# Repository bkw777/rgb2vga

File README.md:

# rgb2vga
Convert 15khz RGB to 31khz VGA

Uses Altera DE0-Nano FPGA development board to convert analog 15Khz RGB signal to VGA 31Khz 256 color.

This is a modified version of the original [RGB2VGA by Luis Felipe da Costa Antoniosi](https://sites.google.com/site/tandycocoloco/fpga-rgb2vga).  
<!-- (Archived original site [archive.org](https://web.archive.org/web/https://sites.google.com/site/tandycocoloco/rgb2vga)) -->

The electronics and fpga code are the same as the original.

The resistor values are from [Roger Taylor](http://www.cococommunity.net/vga-for-the-coco-3/).

The physical layout is changed to make a more compact package and to build-in the two modifications described in the original docs.

The schematic and pcb layout are re-drawn from scratch in KiCad to provide editable source files.

The VHDL source is just a fork of [the original](https://github.com/lfantoniosi/rgb2vga) but with all of the non-source files cleaned out.  
The VHDL does compile and you can generate a new working rgb2vga.jic from it. But as noted by Roger Taylor, you may want to use the original JIC file from Luis anyway because it may be more stable. There is a preseved copy of Luis's original rgb2vga.jic in [vhdl/Original_JIC](vhdl/Original_JIC).

The enclosure is mine, and the OpenSCAD source is included.

Video showing v003 in action.  

Alternate enclosure top with screws and nuts for the artifact switch instead of melted posts.

<!-- [PCB from OSHPark]()  -->
[PCB and Enclosure from PCBWAY](https://www.pcbway.com/project/shareproject/de0_nano_fpga_rgb2vga.html)  

[BOM from DigiKey](https://www.digikey.com/short/wv89d9fv)  

The BOM does not include R29 or C4, which you normally do not populate.  
<!-- 
R29 and C4 provide a 500khz lowpass filter from the LM1881 datasheet.  
If you want to add the lowpass filter, remember to cut the trace in the middle of the R29 footprint.  
I have no idea if the lowpass filter is desired or not. It's in the LM1881 datasheet and it sounds like a good idea since the computer is full of 1+ mhz signals, but I have not actually tested that addition yet.
-->

<!-- 
[DE0-Nano](http://www.terasic.com.tw/cgi-bin/page/archive.pl?Language=English&No=593)
When searching other sources like ebay, don't accidentally get **DE0-Nano-SoC**, that's something else.
-->

<!--
## Through-Hole Version

[Through-Hole BOM from DigiKey](https://www.digikey.com/short/5mq32b7z)
-->

[PCB Gerbers, FPGA Firmware, Enclosure STLs](../../releases/)

# Directions  
## Building the PCB  
- Remove pin #6 from the 2x5 coco3 rgb connector before soldering. Pin #6 is the center pin on the bottom row, opposite/away from the polarity notch.  
- Solder trim pot R24 on the bottom side, and flush cut and re-flow to smooth domes, before R13, R15, R16.  
- Solder the LM1881 U1 before any of the other parts around it.  
- Solder the Artifact switch SW2 before the 3-pin header J7.  
- Solder remaining parts in any order.  

## Programming the DE0-Nano  
Below is the minimum directions and minimum download possible, using the stand-alone Quartus programmer app and the pre-compiled firmware.  
Alternatively, [compile the firmware from the vhdl source](compile_vhdl.md).

### Install the Quartus Standalone Programmer  
https://fpgasoftware.intel.com/  
Select edition: Lite -> Additional Software -> Quartus Prime Programmer and Tools  
(For Linux, install: Individual Files -> Quartus Prime, not the stand-alone programmer package. The stand-alone Quartus programmer package for Linux is broken, missing ```libprotobuf.so.14.0.0```)

### Download the firmware
Download ```rgb2vga.jic``` from [releases](../../releases/)  

### Program the DE0-Nano  
Connect the usb cable  
Launch the Quartus Programmer app  
Hardware Setup... -> USB-Blaster  
Add File... -> ```rgb2vga.jic```  
Tick "Program/Configure"  
Start  

## Assemble
- Remove the acrylic cover and short upper stand-offs from the DE0-Nano. If using the printed enclosure, remove the lower stand-offs too. If not using the printed enclosure, keep the longer bottom standoffs, replace the short upper standoffs with the screws from the cover.  
- Put the RGB2VGA and DE0-Nano together with the trim pot on the same side as the USB connector.  
- For TANDY Color Computer 3, turn all dip switches off. For most games, turn the Artifact switch on. If using the printed enclosure with enclosure artifact switch, set the pcb artifact switch to OFF.  
- Turn the trim pot to 50%.  
- Insert the IDC pin block-off plugs into pin #6 on each end of the ribbon cable. Pin #6 is the center pin on the row opposite/away from the the polarity bump.  

## Enclosure
The source for the enclosure is the [rgb2vga.scad](case/rgb2vga.scad) OpenSCAD file.

The bottom part of the enclosure has screw holes that will accept the M3 screws that came on the rgb2vga, but the screws are not needed. You can simply remove all hardware parts from the DE0-Nano, put the DE0-Nano + rgb2vga in the case and snap it together.

## Artifact Switch
Cut the 3-pin female jumper cable in half. Set one half aside, it won't be used.

Take one half and solder the cut ends to the slide switch as per the diagram on the silk screen on the bottom of the PCB.

Place the switch onto the posts inside the top cover.  
There will be excess plastic underneath the two mounting posts, preventing the switch from seating flat.  
Just heat the switch flanges with the soldering iron to melt the switch into place flat to the inside wall.

Melt the posts with a soldering iron to secure the switch to the top cover.  

Plug the remaining 3-pin female plug onto the 3-pin male header on the pcb.  

Set the small artifact switch on the pcb to the "OFF" position before closing up the enclosure.

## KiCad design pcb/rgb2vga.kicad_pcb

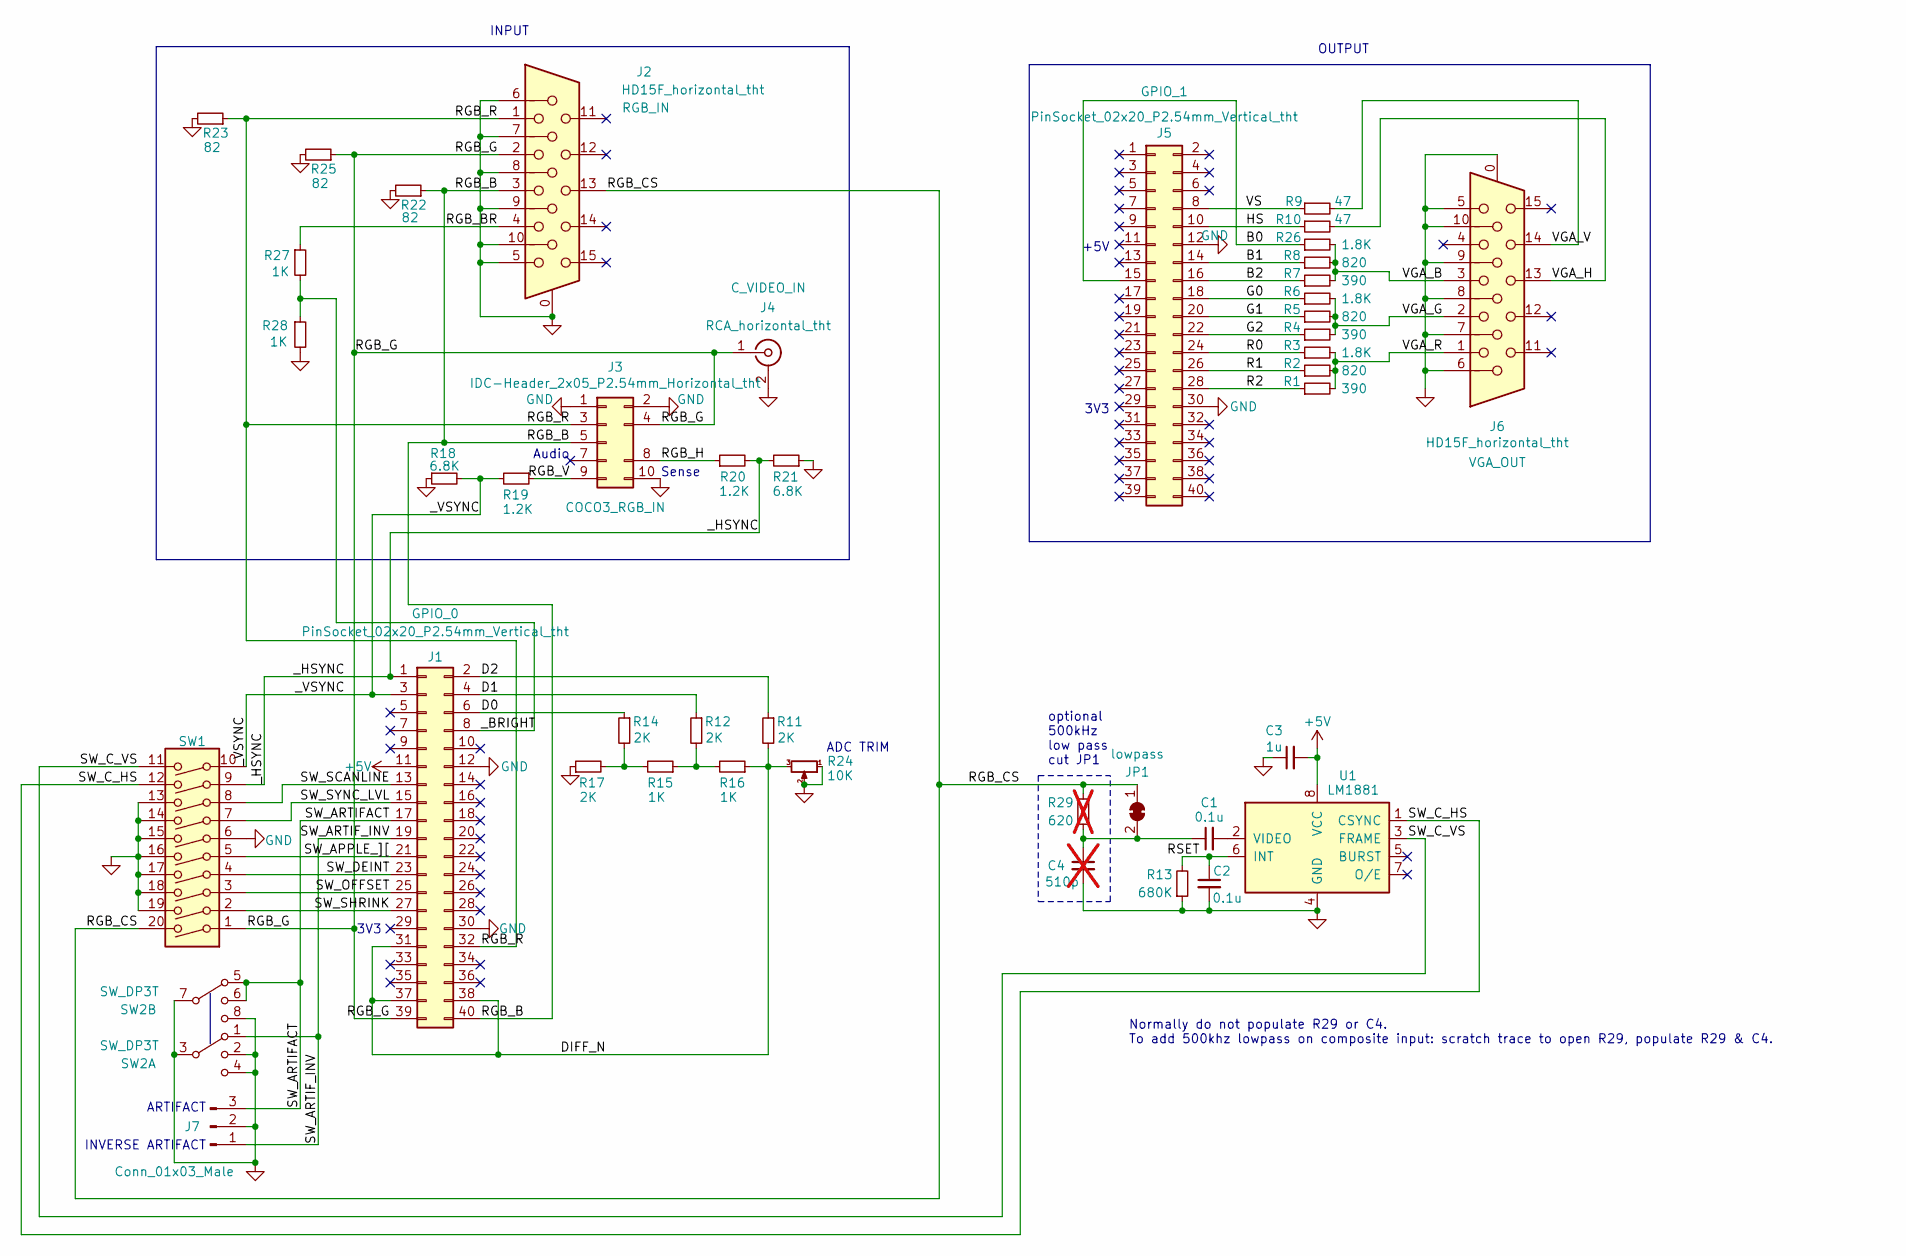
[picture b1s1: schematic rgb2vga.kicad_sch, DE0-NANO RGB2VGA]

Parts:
C1, C2: 0.1u; C_0805; MPN KGM21NR71H104JT
C3: 1u; C_0805; MPN CL21B105KAFNNNE
C4: 510p; C_0805; MPN C0805C511F3HAC7800; not fitted
J1, J5: PinSocket_02x20_P2.54mm_Vertical_tht; PinSocket_2x20_P2.54mm_Polarized_Vertical; MPN SFH11-PBPC-D20-ST-BK
J2, J6: HD15F_horizontal_tht; HD15-SN-25; MPN HD15-SN-25
J3: IDC-Header_2x05_P2.54mm_Horizontal_tht; IDC-Header_2x05_P2.54mm_Horizontal COCO3 KEYED; MPN 302-R101
J4: RCA_horizontal_tht; RCA; MPN RCJ-014
J7: Conn_01x03_Male; PinHeader_1x03_P2.54mm_Horizontal; MPN PRPC003SBAN-M71RC
JP1: lowpass; JP_0805
R1, R4, R7: 390; R_0805; MPN ERA-6AEB391V
R2, R5, R8: 820; R_0805; MPN ERA-6AEB821V
R3, R6, R26: 1.8K; R_0805; MPN ERA-6AEB182V
R9, R10: 47; R_0805; MPN ERA-6AEB470V
R11, R12, R14, R17: 2K; R_0805; MPN ERA-6AEB202V
R13: 680K; R_0805; MPN ERA-6AEB684V
R15, R16, R27, R28: 1K; R_0805; MPN ERA-6AEB102V
R18, R21: 6.8K; R_0805; MPN ERA-6AEB682V
R19, R20: 1.2K; R_0805; MPN ERA-6AEB122V
R22, R23, R25: 82; R_0805; MPN ERA-6AEB820V
R24: 10K; Potentiometer_Bourns_3006P_Horizontal; MPN 3006P-1-103LF
R29: 620; R_0805; MPN ERA-6AEB621V; not fitted
SW1: SW_DIP_x10; SW_DIP_SPSTx10_Slide_6.7_8.61_P2.54_LowProfile; MPN DS04-254-2-10BK-SMT
SW2: SW_DP3T; SW_DP3T_CK_JS203011JAQN; MPN CL-SB-23A-11T
U1: LM1881; SOIC-8_4x5; MPN LM1881MX/NOPB

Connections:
+5V: C3.2, J1.11, U1.8 (VCC)
/B0: J5.15, R26.1
/B1: J5.14, R8.1
/B2: J5.16, R7.1
/D0: J1.6, R14.1
/D1: J1.4, R12.1
/D2: J1.2, R11.1
/DIFF_N: J1.31, J1.37, J1.38, R11.2, R16.1, R24.3
/G0: J5.18, R6.1
/G1: J5.20, R5.1
/G2: J5.22, R4.1
/HS: J5.10, R10.1
/R0: J5.24, R3.1
/R1: J5.26, R2.1
/R2: J5.28, R1.1
/RGB_B: J1.40, J2.3, J3.5, R22.1
/RGB_BR: J2.4, R27.1
/RGB_CS: J2.13, JP1.1 (A), R29.1, SW1.20
/RGB_G: J1.39, J2.2, J3.4, J4.1 (In), R25.1, SW1.1
/RGB_H: J3.8, R20.1
/RGB_R: J1.32, J2.1, J3.3, R23.1
/RGB_V: J3.9, R19.1
/RSET: C2.1, R13.2, U1.6 (INT)
/SW_APPLE_][: J1.21, SW1.5
/SW_ARTIFACT: J1.17, J7.3, SW2.5, SW2.6
/SW_ARTIF_INV: J1.19, J7.1, SW2.1
/SW_C_HS: SW1.12, U1.1 (CSYNC)
/SW_C_VS: SW1.11, U1.3 (FRAME)
/SW_DEINT: J1.23, SW1.4
/SW_OFFSET: J1.25, SW1.3
/SW_SCANLINE: J1.13, SW1.8
/SW_SHRINK: J1.27, SW1.2
/SW_SYNC_LVL: J1.15, SW1.7
/VGA_B: J6.3, R7.2, R8.2, R26.2
/VGA_G: J6.2, R4.2, R5.2, R6.2
/VGA_H: J6.13, R10.2
/VGA_R: J6.1, R1.2, R2.2, R3.2
/VGA_V: J6.14, R9.2
/VS: J5.8, R9.1
/_BRIGHT: J1.8, R27.2, R28.1
/_HSYNC: J1.1, R20.2, R21.2, SW1.9
/_VSYNC: J1.3, R18.2, R19.2, SW1.10
GND: C2.2, C3.1, C4.2, J1.12, J1.30, J2.0, J2.5, J2.6, J2.7, J2.8, J2.9, J2.10, J3.1, J3.2, J3.10, J4.2 (Ext), J5.12, J5.30, J6.0, J6.5, J6.6, J6.7, J6.8, J6.9, J6.10, J7.2, R13.1, R17.1, R18.1, R21.1, R22.2, R23.2, R24.1, R24.2, R25.2, R28.2, SW1.6, SW1.13, SW1.14, SW1.15, SW1.16, SW1.17, SW1.18, SW1.19, SW2.2, SW2.3, SW2.4, SW2.7, SW2.8, U1.4 (GND)
unnamed: C1.1, C4.1, JP1.2 (B), R29.2
unnamed: R12.2, R15.1, R16.2
unnamed: R14.2, R15.2, R17.2
unnamed: C1.2, U1.2 (VIDEO)

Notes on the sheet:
Normally do not populate R29 or C4. To add 500khz lowpass on composite input: scratch trace to open R29, populate R29 & C4.
Audio
3V3
ARTIFACT
INPUT
OUTPUT
Sense
optional 500kHz low pass cut JP1
+5V
ADC TRIM
INVERSE ARTIFACT

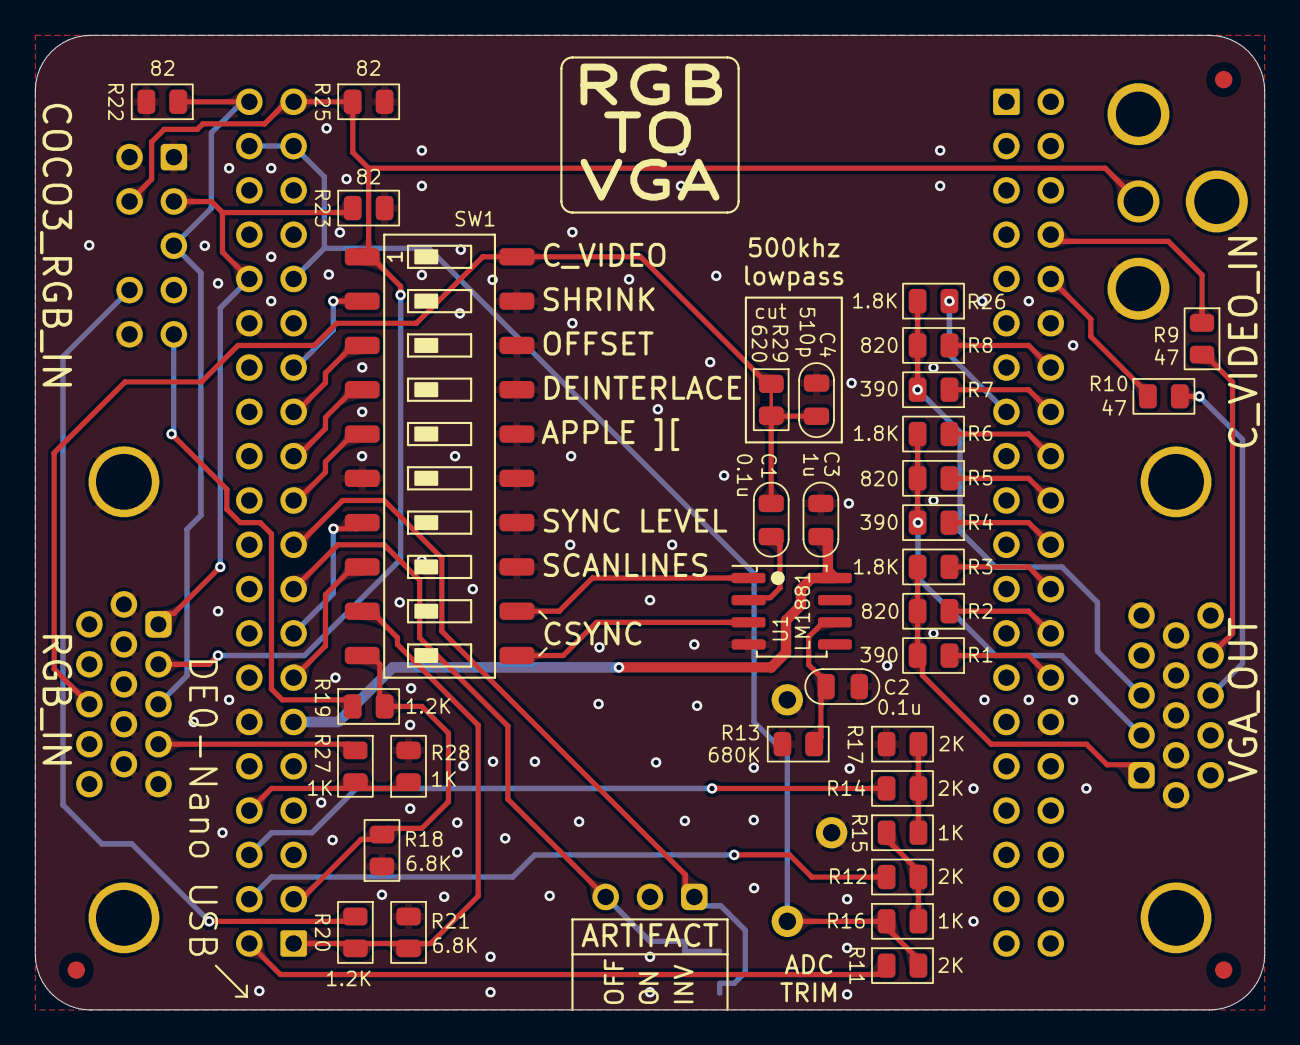
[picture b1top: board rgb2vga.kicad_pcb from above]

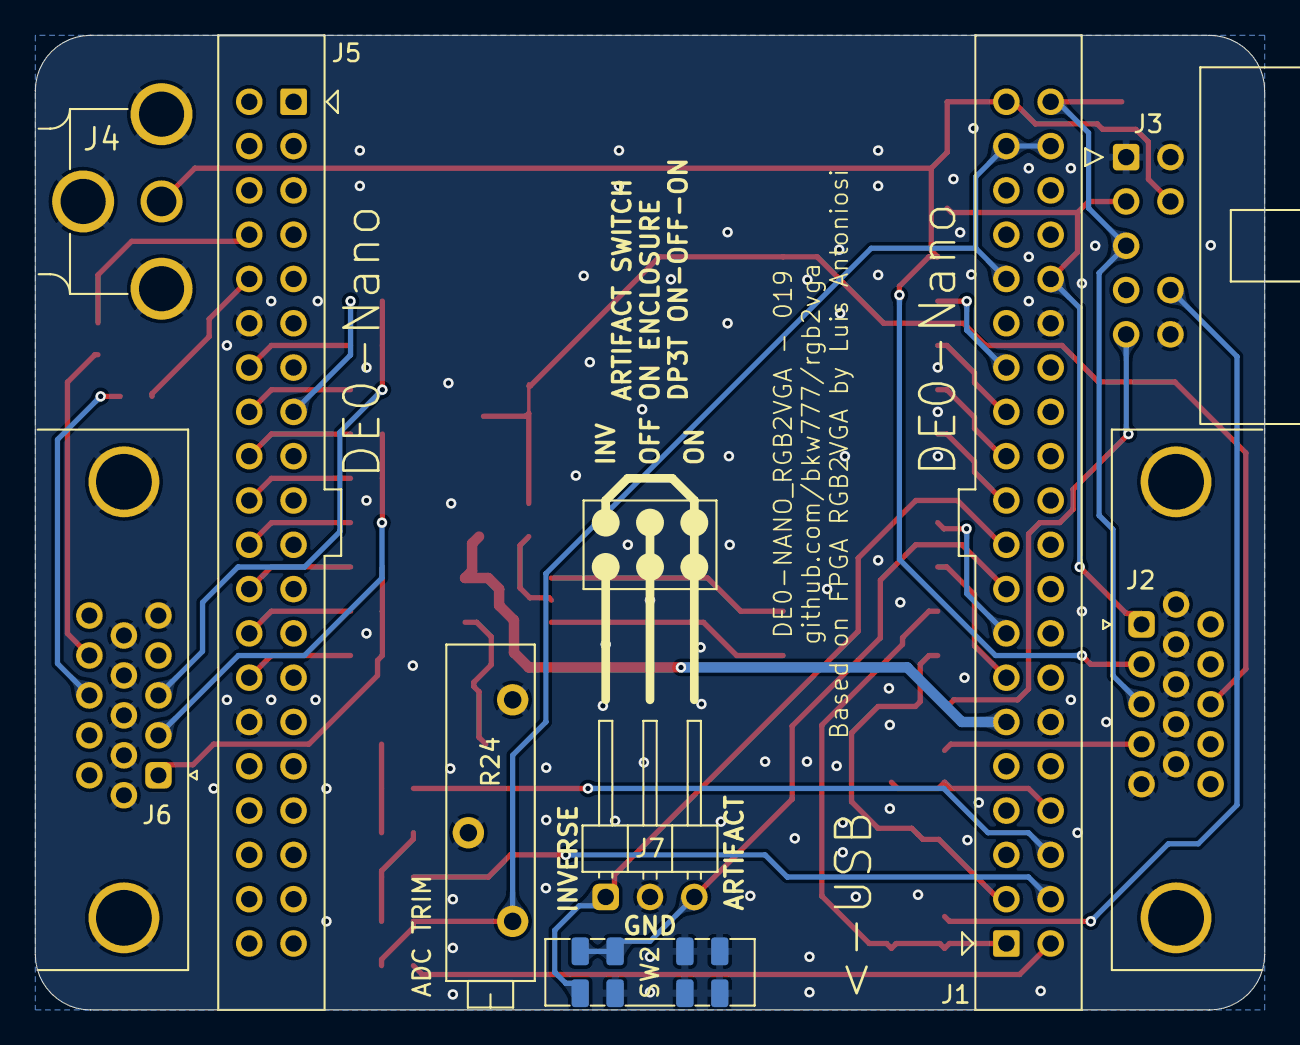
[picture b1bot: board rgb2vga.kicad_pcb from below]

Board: 2 copper layers, 70.5 x 55.9 mm, 45 parts (9 on the bottom side), 47 nets.

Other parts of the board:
DE0-Nano: DE0-Nano_bare

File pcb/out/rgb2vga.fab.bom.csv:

"Reference","Value","Datasheet","Footprint","Qty","DNP","MPN"
"C1,C2","0.1u","~","000_LOCAL:C_0805","2","","KGM21NR71H104JT"
"C3","1u","~","000_LOCAL:C_0805","1","","CL21B105KAFNNNE"
"J1,J5","PinSocket_02x20_P2.54mm_Vertical_tht","datasheets/DE0-Nano.pdf","000_LOCAL:PinSocket_2x20_P2.54mm_Polarized_Vertical","2","","SFH11-PBPC-D20-ST-BK"
"J2,J6","HD15F_horizontal_tht","datasheets/hdxx-sn-25.pdf","000_LOCAL:HD15-SN-25","2","","HD15-SN-25"
"J3","IDC-Header_2x05_P2.54mm_Horizontal_tht","datasheets/coco3.pdf","000_LOCAL:IDC-Header_2x05_P2.54mm_Horizontal COCO3 KEYED","1","","302-R101"
"J4","RCA_horizontal_tht"," ~","000_LOCAL:RCA","1","","RCJ-014"
"J7","Conn_01x03_Male","~","000_LOCAL:PinHeader_1x03_P2.54mm_Horizontal","1","","PRPC003SBAN-M71RC"
"R1,R4,R7","390","~","000_LOCAL:R_0805","3","","ERA-6AEB391V"
"R2,R5,R8","820","~","000_LOCAL:R_0805","3","","ERA-6AEB821V"
"R3,R6,R26","1.8K","~","000_LOCAL:R_0805","3","","ERA-6AEB182V"
"R9,R10","47","~","000_LOCAL:R_0805","2","","ERA-6AEB470V"
"R11,R12,R14,R17","2K","~","000_LOCAL:R_0805","4","","ERA-6AEB202V"
"R13","680K","~","000_LOCAL:R_0805","1","","ERA-6AEB684V"
"R15,R16,R27,R28","1K","~","000_LOCAL:R_0805","4","","ERA-6AEB102V"
"R18,R21","6.8K","~","000_LOCAL:R_0805","2","","ERA-6AEB682V"
"R19,R20","1.2K","~","000_LOCAL:R_0805","2","","ERA-6AEB122V"
"R22,R23,R25","82","~","000_LOCAL:R_0805","3","","ERA-6AEB820V"
"R24","10K","datasheets/3006.pdf","000_LOCAL:Potentiometer_Bourns_3006P_Horizontal","1","","3006P-1-103LF"
"SW1","SW_DIP_x10","datasheets/ds04-254-smt.pdf","000_LOCAL:SW_DIP_SPSTx10_Slide_6.7_8.61_P2.54_LowProfile","1","","DS04-254-2-10BK-SMT"
"SW2","SW_DP3T","datasheets/cl-sb.pdf","000_LOCAL:SW_DP3T_CK_JS203011JAQN","1","","CL-SB-23A-11T"
"U1","LM1881","datasheets/LM1881.pdf","000_LOCAL:SOIC-8_4x5","1","","LM1881MX/NOPB"
"C4","510p","~","000_LOCAL:C_0805","1","DNP","C0805C511F3HAC7800"
"R29","620","~","000_LOCAL:R_0805","1","DNP","ERA-6AEB621V"

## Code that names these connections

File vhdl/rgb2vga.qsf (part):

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set_location_assignment PIN_R6 -to DRAM_DQM[0]
set_location_assignment PIN_L2 -to DRAM_RAS_N
set_location_assignment PIN_C2 -to DRAM_WE_N
set_location_assignment PIN_B8 -to VSYNC
set_location_assignment PIN_A8 -to HSYNC
set_location_assignment PIN_T12 -to VGAVS
set_location_assignment PIN_K16 -to VGAG2
set_location_assignment PIN_L15 -to VGAR0
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set_location_assignment PLL_1 -to "pll_speccy:pll_inst"
set_location_assignment PLL_1 -to "pll_coco3:pll_inst"
set_location_assignment PIN_R10 -to VGAB2
set_location_assignment PIN_B4 -to BRIGHT
set_instance_assignment -name CURRENT_STRENGTH_NEW "MINIMUM CURRENT" -to D0
set_instance_assignment -name CURRENT_STRENGTH_NEW "MINIMUM CURRENT" -to D1
set_instance_assignment -name CURRENT_STRENGTH_NEW "MINIMUM CURRENT" -to D2
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
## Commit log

2021-11-01 initial
2021-11-01 resistor values, routing
2021-11-05 recreated schematic, add rgbi resistors, 3d models, digikey bom, Roger Taylor resistor values
2021-11-05 schematic in readme
2021-11-05 add some net labels and fix several errors in the schematic didn't match the pcb
2021-11-05 readme schematic
2021-11-05 remove accidental junction on DIFFB
2021-11-05 spread schematic out a little
2021-11-05 neaten schematic
2021-11-06 net labels
2021-11-06 move caps near lm1881
2021-11-07 layout grid alignmen
2021-11-07 link schematic to pcb, remove unused footprints and models
2021-11-07 slight pcb touchup
2021-11-07 rearrange R22 R25
2021-11-07 better 3d model for vga connector
2021-11-10 vga connector 3d model
2021-11-10 move R26
2021-11-12 fix spacing between GPIO0 and GPIO1
2021-11-15 zone fill to new pcb edge
2021-11-16 gpio_1 position
2021-11-16 traces and pours around gpio_1
2021-11-16 readme
2021-11-16 models
2021-11-18 add DE0-Nano virtual component
2021-11-19 low profile version
2021-11-19 renders, small routing touchup
2021-11-19 silkscreen
2021-11-19 gpio headers must be 43.4mm apart
2021-11-19 v002.1 - gpio headers must be 43.4mm apart
2021-11-23 kicad gitignore
2021-11-23 remove quartus output files from git
2021-11-23 exclude quartus output files from git
2021-11-23 add sof->jic config for DE0-Nano
2021-11-23 quartus version
2021-11-23 rename coco3 -> rgb2vga
2021-11-26 remove junk quartus output/tmp files
2021-11-26 gitignore junk quartus output/tmp files
2021-11-26 sof-to-jic config for de0-nano
2021-11-26 quartus lite 21
2021-11-26 readme, remove unneeded files
2021-11-26 update from main
2021-11-26 net names, clearance for idc plugs around gpio headers
2021-11-28 SW2 for Artifact
2021-11-29 align & center parts, silkscreen
2021-12-01 isolisolate r,g,b in a little better, cosmetic alignment
2021-12-11 exclude 3d models except in footprints
2021-12-11 enclosure
2021-12-11 remote artifact sw
2021-12-11 exclude 3d models outside of footprints
2021-12-11 3d printable enclosure
2021-12-11 case doesn't fit v003
2021-12-11 add 3d-printable enclosure
2021-12-11 remove accidentally added case dir, again
2021-12-14 better enclosure
2021-12-14 update 3d print link
2021-12-14 enclosure render
2021-12-16 case rounded box & fillets
2021-12-16 readme, enclosure 009.3 craftcloud
2021-12-16 quartus IP update
2021-12-17 add 3-pin header to bom csv
2021-12-17 silkscreen for off-board artifact switch
2021-12-17 bottom side picture
2021-12-17 move coco3 rgb port slightly. silkscreen
2021-12-17 009 readme to avoid merge conflict
2021-12-28 port positions and silkscreen
2021-12-28 enclosure fillets
2021-12-28 small schematic tidy
2021-12-28 right-angle usb cable
2021-12-28 enclosure scad default view
2021-12-31 009rc8
2022-01-02 enclosure artifact switch
2022-01-02 enclosure text
2022-01-11 printed nuts bore diameter
2022-01-11 update craftcloud link
2022-01-19 ignore slicer gcode files
2022-01-19 nut dimensions, inhibit surface text for fdm
2022-01-20 case v013, makefile, switch mount & nuts
2022-01-20 remove flat-head screw option - conical head would split layers
2022-01-21 enclosure fit and configurable switch mount
2022-01-22 remove print profile
2023-02-27 kicad 6
2023-02-28 pics
2024-01-05 multi-turn DAC trimmer pot
2024-01-08 SMT passives, add lowpass, decouple lm1881
2024-03-07 kicad 8
2024-07-26 fix bom had 680 instead of 680K for R13
2024-07-26 fiducials, pics
2024-08-06 C4 510p, dnp fiducials, pnp export
2024-08-07 export bom, centroid
2024-08-30 silkscreen & pics
2024-08-30 include Luis's original .jic
2024-08-31 rename msx switch to offset
